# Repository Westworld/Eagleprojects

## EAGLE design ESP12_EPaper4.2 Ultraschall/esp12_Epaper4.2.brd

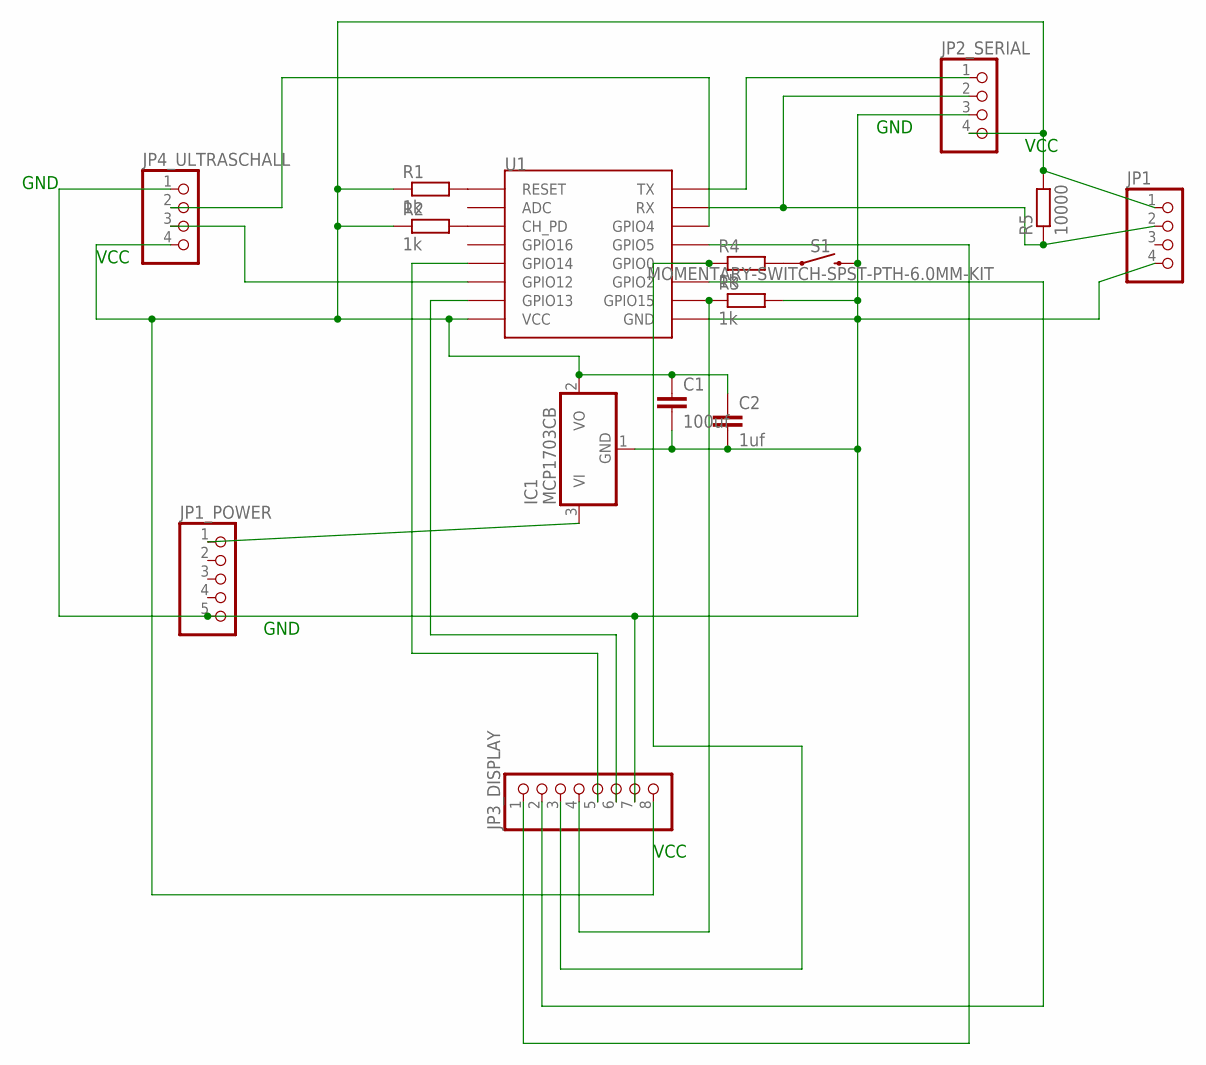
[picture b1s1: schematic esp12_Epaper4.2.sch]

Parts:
C1: 100uf; C025-050X050
C2: 1uf; C025-050X050
IC1: MCP1703CB; SOT23
JP1, JP4_ULTRASCHALL: PINHD-1X4; 1X04
JP1_POWER: PINHD-1X5; 1X05
JP2_SERIAL: PINHD-1X4/90; 1X04/90
JP3_DISPLAY: PINHD-1X8/90; 1X08/90
R1, R2, R3, R4: 1k; R1206
R5: 10000; M1206
S1: MOMENTARY-SWITCH-SPST-PTH-6.0MM-KIT; TACTILE_SWITCH_PTH_6.0MM_KIT
U1: ESP12

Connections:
GND: C1.2, C2.2, IC1.1 (GND), JP1.4, JP1_POWER.5, JP2_SERIAL.3, JP3_DISPLAY.7, JP4_ULTRASCHALL.1, R3.2, S1.3 (2), U1.GND
unnamed: R1.2, U1.RESET
unnamed: R2.2, U1.CH_PD
unnamed: JP3_DISPLAY.3, R4.1, U1.GPIO0
unnamed: JP4_ULTRASCHALL.2, U1.GPIO4
unnamed: R4.2, S1.1
unnamed: JP2_SERIAL.1, U1.TX
unnamed: JP1.2, JP2_SERIAL.2, R5.1, U1.RX
unnamed: IC1.3 (VI), JP1_POWER.1
unnamed: JP3_DISPLAY.5, U1.GPIO14
unnamed: JP3_DISPLAY.6, U1.GPIO13
unnamed: JP3_DISPLAY.2, U1.GPIO2
unnamed: JP3_DISPLAY.1, U1.GPIO5
unnamed: JP4_ULTRASCHALL.3, U1.GPIO12
unnamed: JP3_DISPLAY.4, R3.1, U1.GPIO15
VCC: C1.1, C2.1, IC1.2 (VO), JP1.1, JP2_SERIAL.4, JP3_DISPLAY.8, JP4_ULTRASCHALL.4, R1.1, R2.1, R5.2, U1.VCC

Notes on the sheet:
GND
VCC

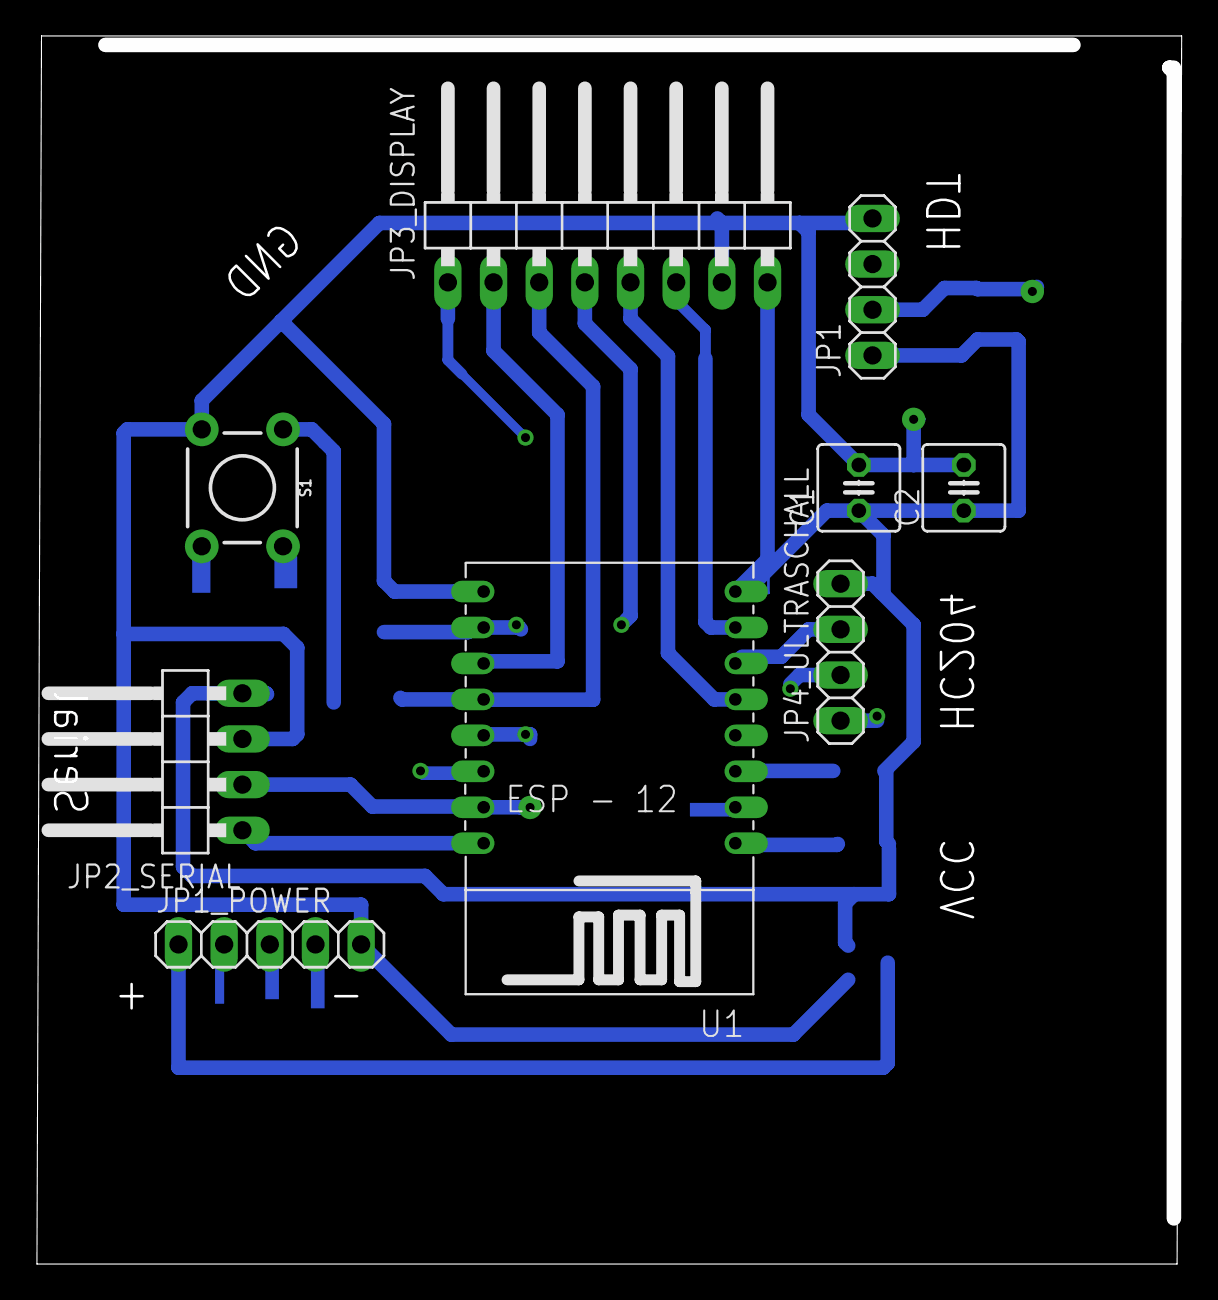
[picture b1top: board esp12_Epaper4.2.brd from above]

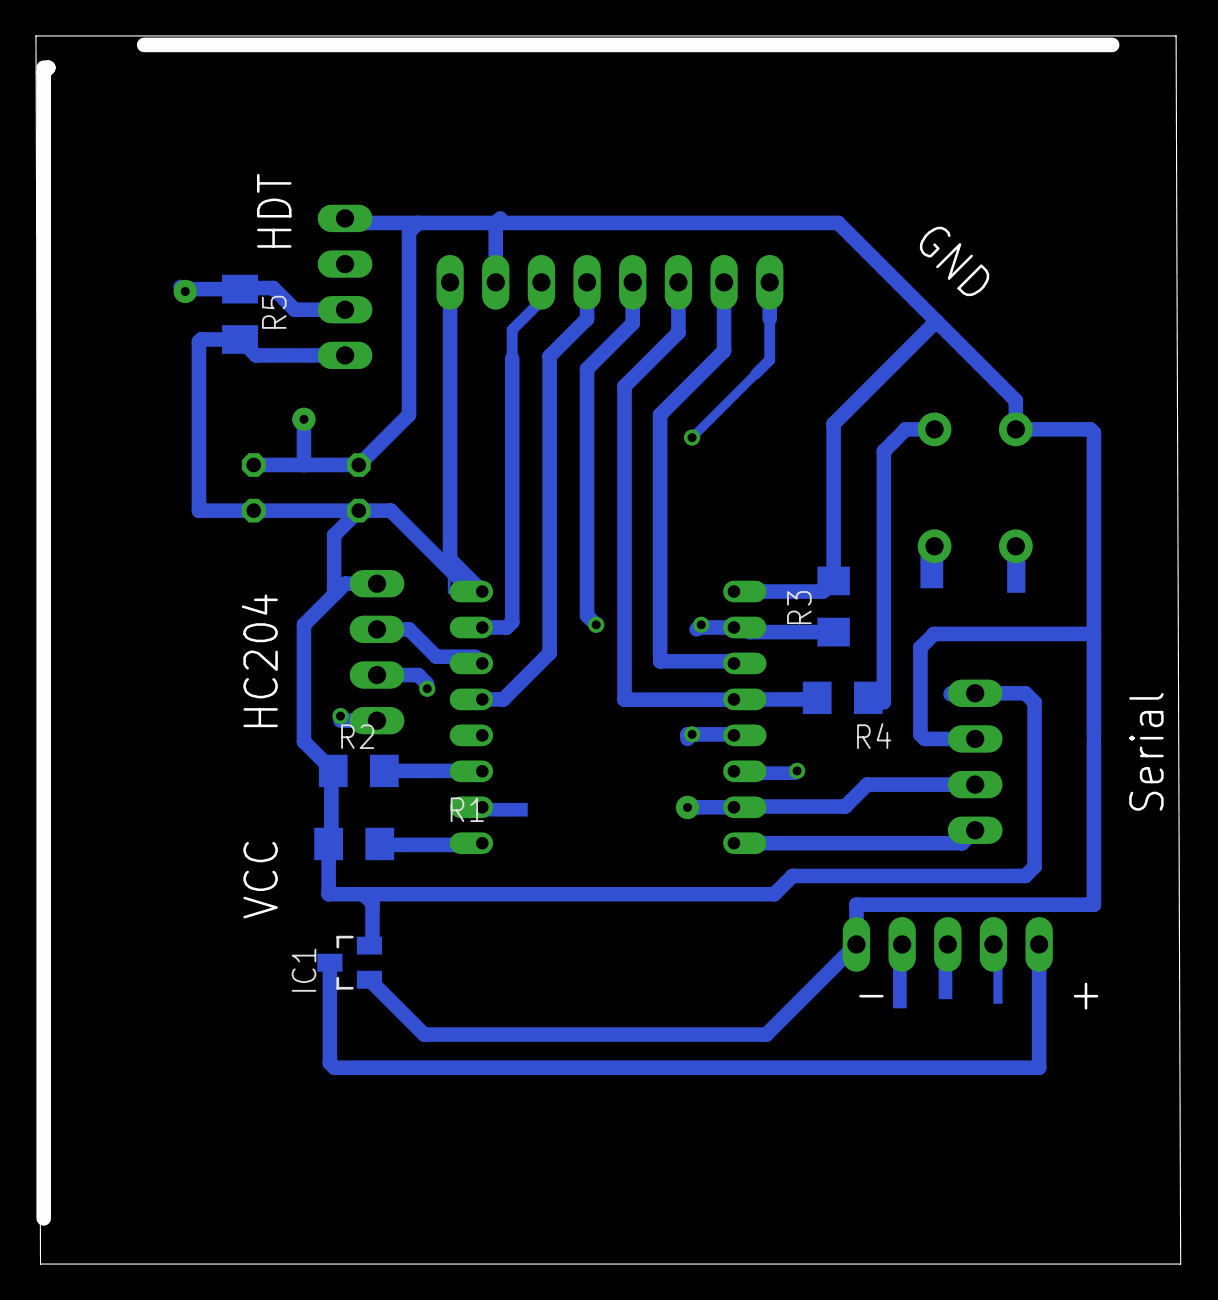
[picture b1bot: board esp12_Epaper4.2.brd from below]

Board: 2 copper layers, 63.7 x 68.3 mm, 15 parts (6 on the bottom side), 16 nets.

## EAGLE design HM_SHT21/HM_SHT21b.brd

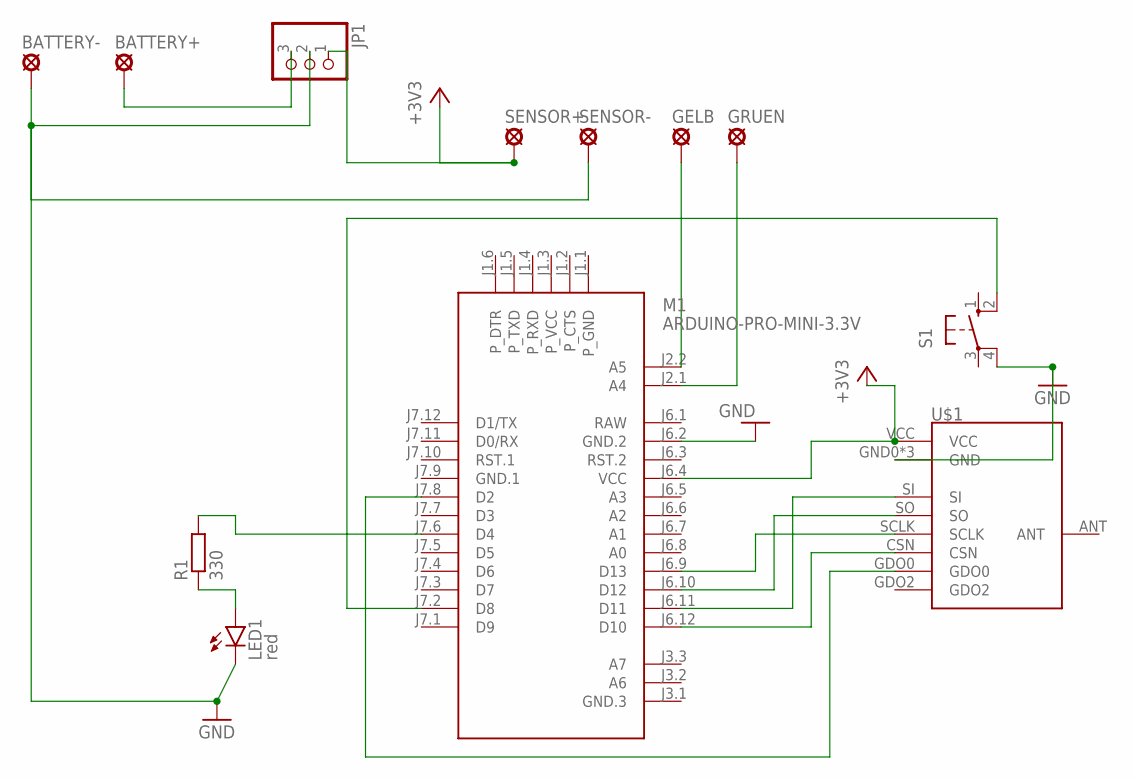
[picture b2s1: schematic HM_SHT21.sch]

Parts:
BATTERY+: LSP11
BATTERY-: LSP11
GELB: LSP11
GRUEN: LSP11
JP1: PINHD-1X3; 1X03
LED1: red; LED5MM
M1: ARDUINO-PRO-MINI-3.3V; ARDUINO-PRO-MINI
R1: 330; 0204/7
S1: 10-XX; B3F-10XX
SENSOR+: LSP11
SENSOR-: LSP11
U$1: CC1101

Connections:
+3V3: JP1.1, M1.J6.4 (VCC), SENSOR+.MP, U$1.VCC
GND: BATTERY-.MP, JP1.2, LED1.K (C), M1.J6.2 (GND.2), S1.4 (P1), SENSOR-.MP, U$1.GND0 (GND), U$1.GND1 (GND), U$1.GND2 (GND)
GND.1: M1.J7.9 (GND.1)
unnamed: M1.J6.12 (D10), U$1.CSN
unnamed: M1.J7.8 (D2), U$1.GDO0
unnamed: M1.J6.11 (D11), U$1.SI
unnamed: M1.J6.10 (D12), U$1.SO
unnamed: M1.J6.9 (D13), U$1.SCLK
unnamed: LED1.A, R1.1
unnamed: M1.J7.2 (D8), S1.2 (S1)
unnamed: M1.J7.6 (D4), R1.2
unnamed: GELB.MP, M1.J2.2 (A5)
unnamed: GRUEN.MP, M1.J2.1 (A4)
RAW: M1.J6.1 (RAW)
VIN: BATTERY+.MP, JP1.3

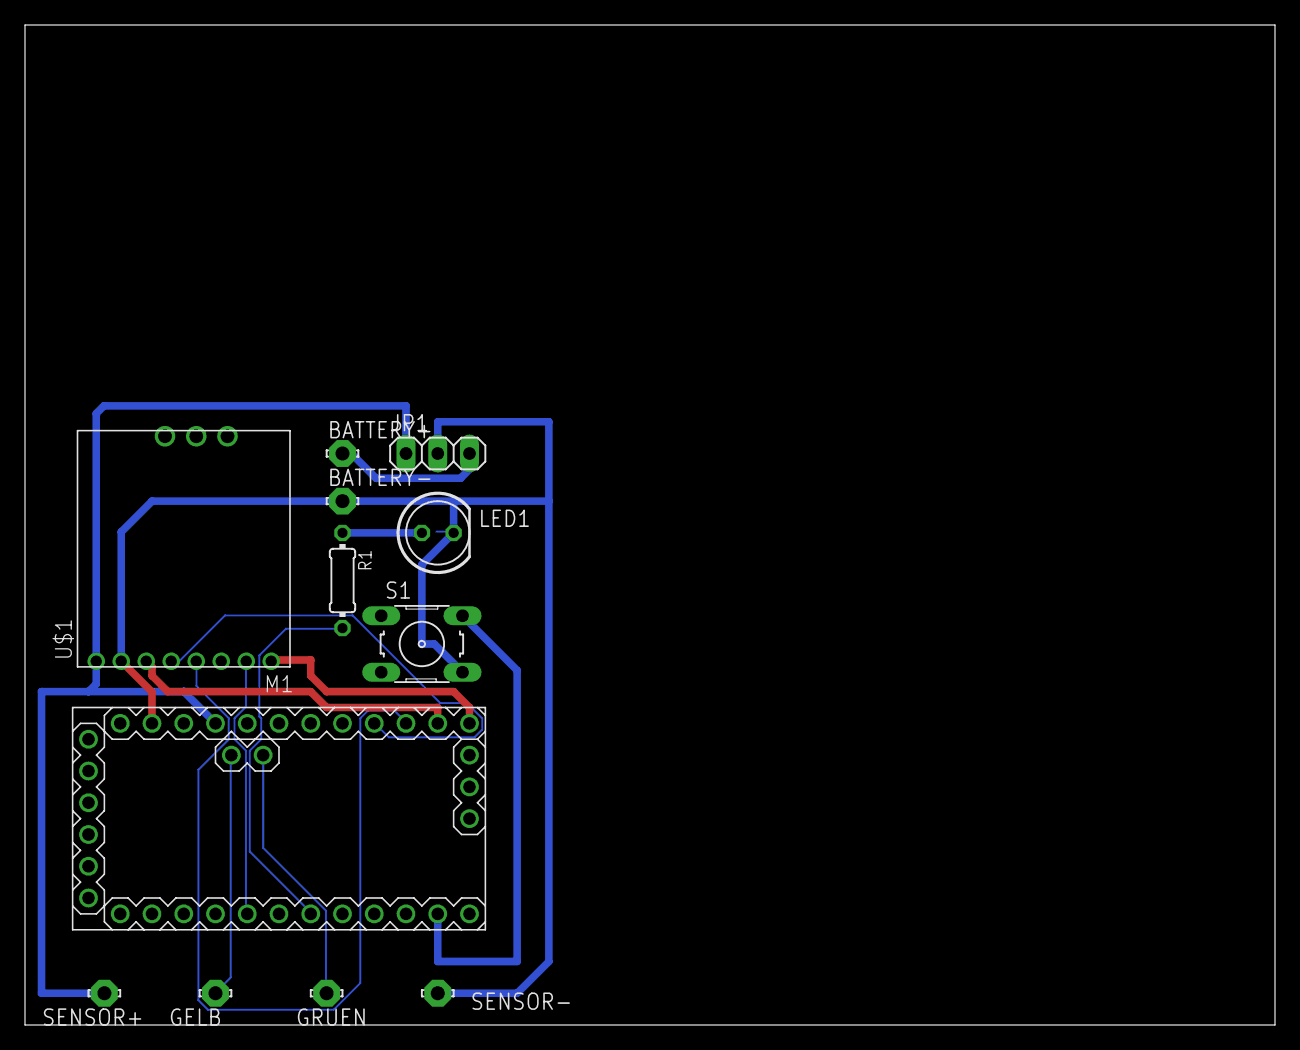
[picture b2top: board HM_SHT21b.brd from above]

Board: 2 copper layers, 100.0 x 80.0 mm, 12 parts (0 on the bottom side), 13 nets.

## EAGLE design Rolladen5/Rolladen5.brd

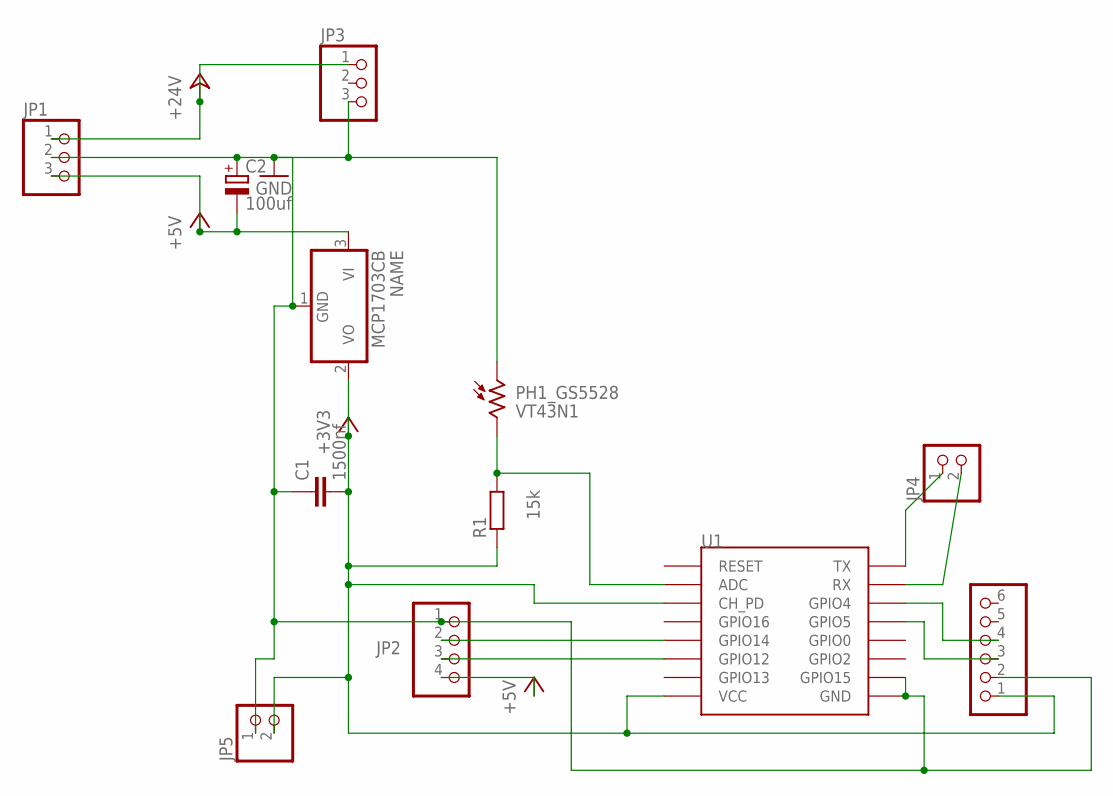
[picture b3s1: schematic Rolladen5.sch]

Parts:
C1: 1500nf; C025-024X044
C2: 100uf; E2,5-6
IC1_MCP1700: MCP1703CB; SOT23
JP1: PINHD-1X3/90; 1X03/90
JP2: PINHD-1X4; 1X04
JP3: PINHD-1X3; 1X03
JP3TMP102: PINHD-1X6; 1X06
JP4, JP5: PINHD-1X2; 1X02
PH1_GS5528: VT43N1; VT400
R1: 15k; 0207/10
U1: ESP12

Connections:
+3V3: C1.2, IC1_MCP1700.2 (VO), JP3TMP102.1, JP5.2, R1.1, U1.CH_PD, U1.VCC
+5V: C2.-, IC1_MCP1700.3 (VI), JP1.3, JP2.4
+24V: JP1.1, JP3.1
GND: C1.1, C2.+, IC1_MCP1700.1 (GND), JP1.2, JP2.1, JP3.3, JP3TMP102.2, JP5.1, PH1_GS5528.1, U1.GND, U1.GPIO15
unnamed: PH1_GS5528.2, R1.2, U1.ADC
unnamed: JP3TMP102.3, U1.GPIO5
unnamed: JP2.3, U1.GPIO12
unnamed: JP4.1, U1.TX
unnamed: JP4.2, U1.RX
unnamed: JP3TMP102.4, U1.GPIO4
unnamed: JP2.2, U1.GPIO14

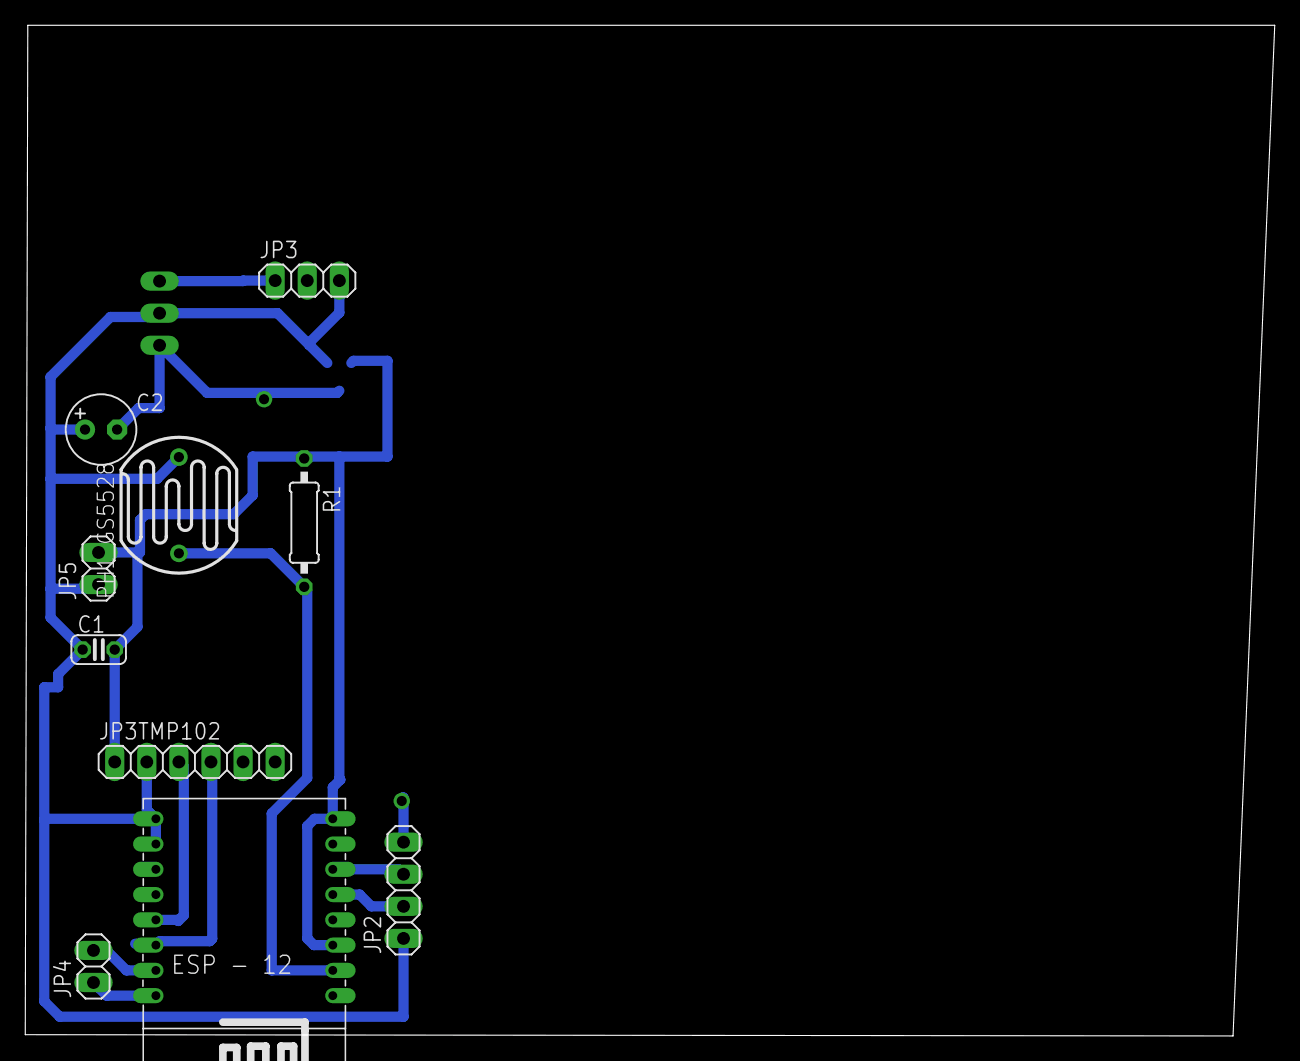
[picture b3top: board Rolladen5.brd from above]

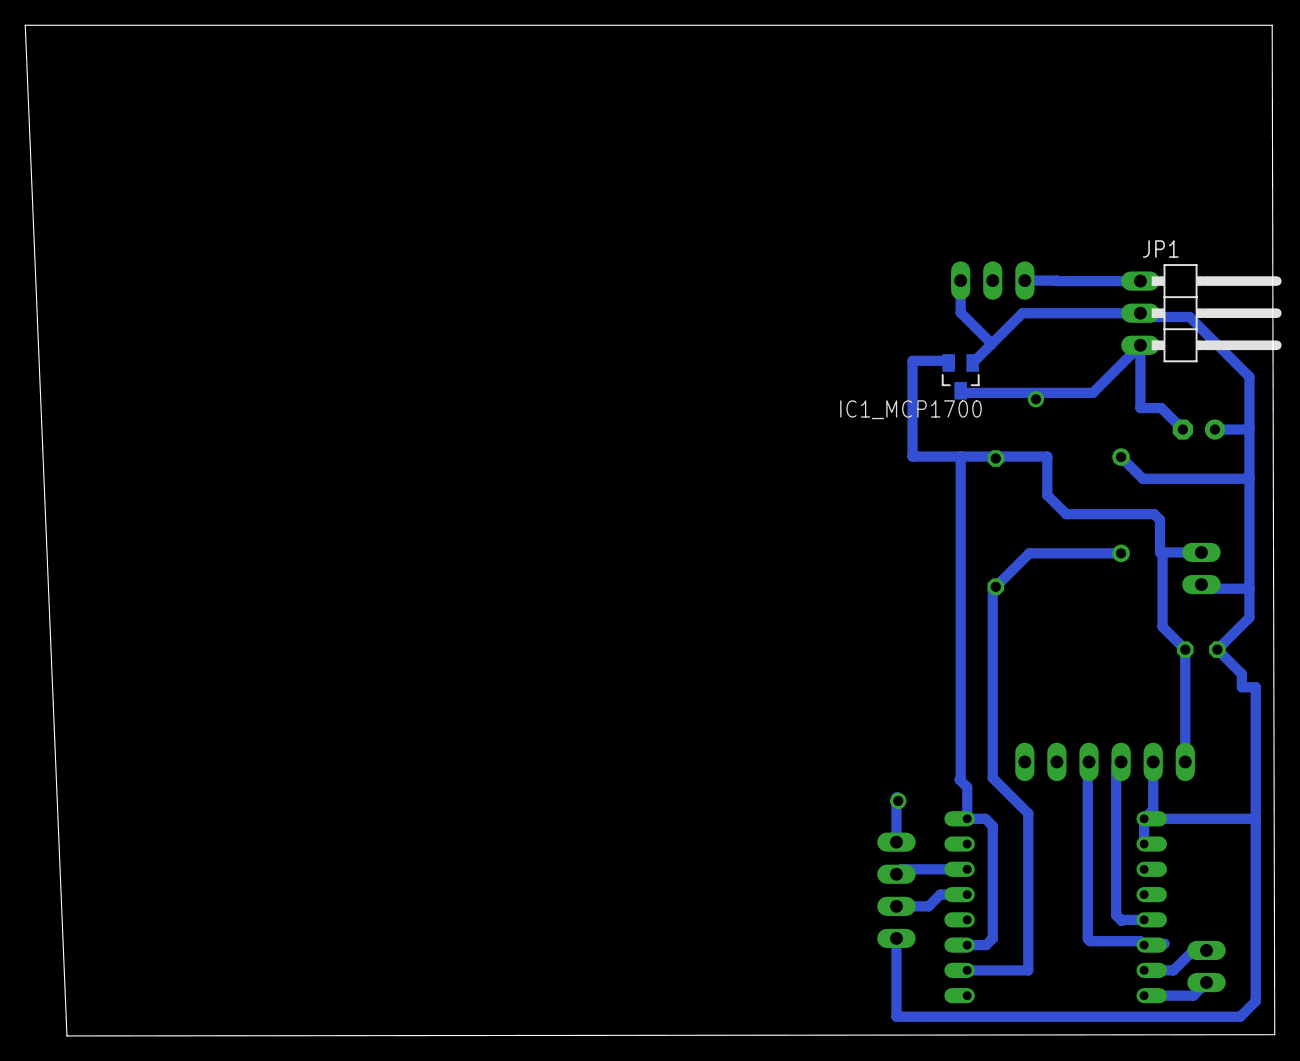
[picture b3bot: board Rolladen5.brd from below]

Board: 2 copper layers, 98.9 x 80.0 mm, 12 parts (2 on the bottom side), 11 nets.

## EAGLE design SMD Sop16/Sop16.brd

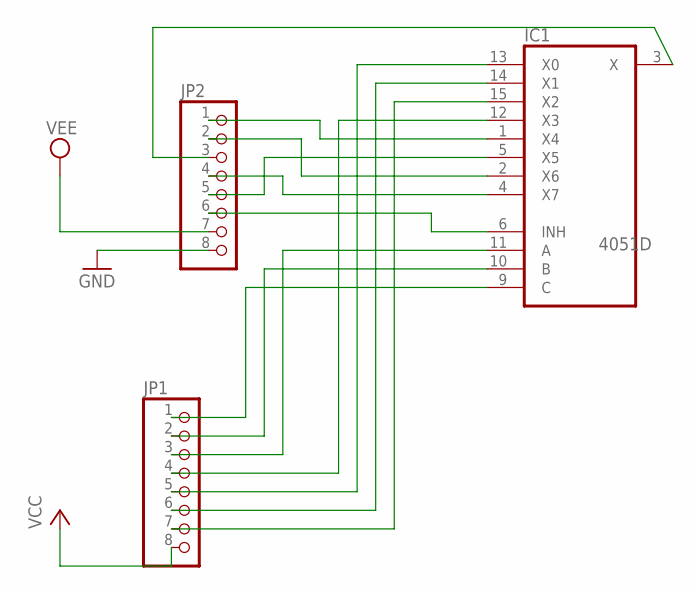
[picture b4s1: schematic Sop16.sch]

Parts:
IC1: 4051D; SO16
JP1, JP2: PINHD-1X8; 1X08

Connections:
GND: IC1.8 (GND), JP2.8
unnamed: IC1.1 (X4), JP2.1
unnamed: IC1.2 (X6), JP2.2
unnamed: IC1.3 (X), JP2.3
unnamed: IC1.4 (X7), JP2.4
unnamed: IC1.5 (X5), JP2.5
unnamed: IC1.6 (INH), JP2.6
unnamed: IC1.9 (C), JP1.1
unnamed: IC1.10 (B), JP1.2
unnamed: IC1.11 (A), JP1.3
unnamed: IC1.12 (X3), JP1.4
unnamed: IC1.13 (X0), JP1.5
unnamed: IC1.14 (X1), JP1.6
unnamed: IC1.15 (X2), JP1.7
VCC: IC1.16 (VCC), JP1.8
VEE: IC1.7 (VEE), JP2.7

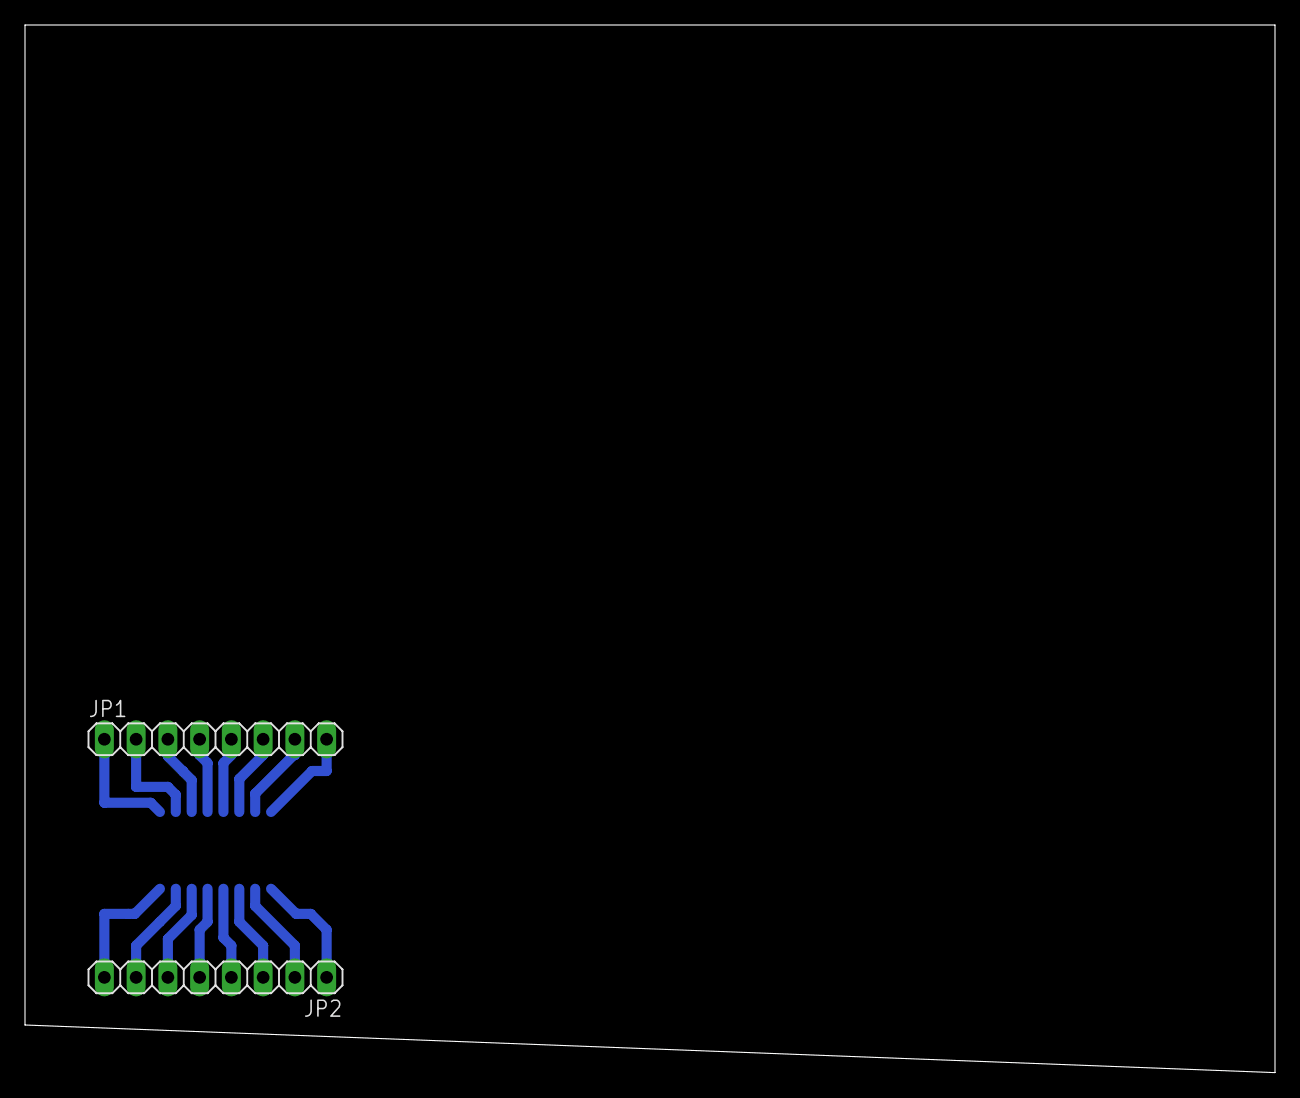
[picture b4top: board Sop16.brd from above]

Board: 2 copper layers, 100.0 x 83.8 mm, 3 parts (1 on the bottom side), 16 nets.

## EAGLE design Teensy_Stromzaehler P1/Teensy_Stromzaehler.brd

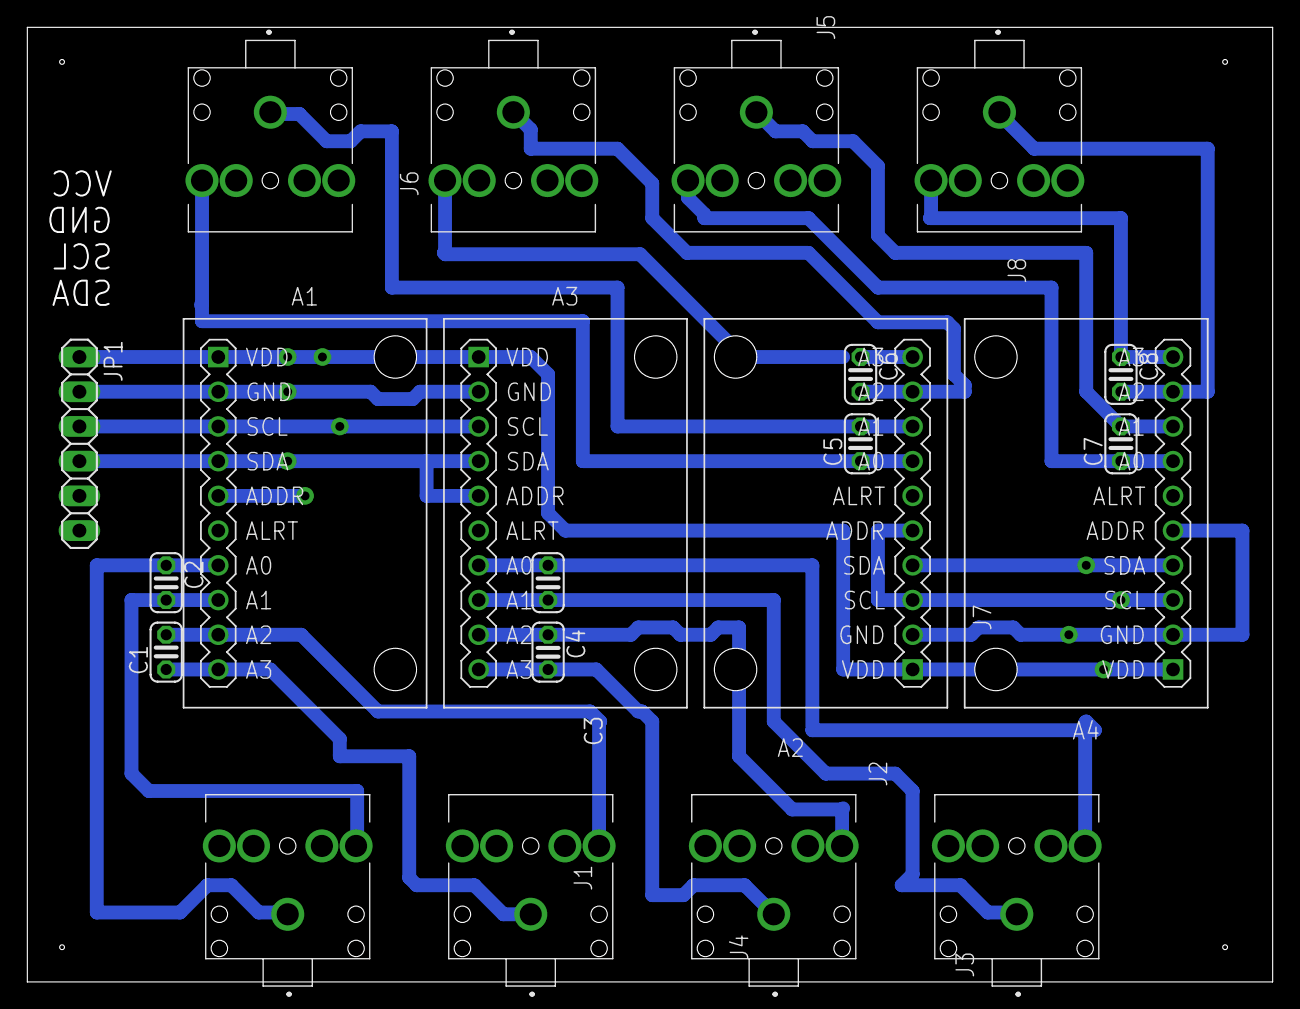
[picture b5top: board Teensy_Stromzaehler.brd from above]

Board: 2 copper layers, 91.1 x 69.8 mm, 21 parts (0 on the bottom side), 20 nets.

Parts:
A1, A2, A3, A4: ADC-4CH-ADS1115
C1, C2, C4, C5, C6, C7, C8: 100nf; C025-024X044
C3: 110nf; C025-024X044
J1, J2, J3, J4, J5, J6, J7, J8: FC68133
JP1: 1X06

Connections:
unnamed: A1.7, C2.1, J2.1
unnamed: A1.8, C2.2, J2.2
unnamed: A1.9, C1.2, J1.2
unnamed: A1.10, C1.1, J1.1
unnamed: A3.8, C3.2, J3.1
unnamed: A3.10, C4.2, J4.1
unnamed: A4.7, C7.1, J5.2
unnamed: A3.7, C3.1, J3.2
unnamed: A1.2, A2.2, A3.2, A4.2, A4.5, JP1.2
unnamed: A2.7, C5.1, J6.2
unnamed: A2.8, C5.2, J6.1
unnamed: A1.3, A2.3, A2.5, A3.3, A4.3, JP1.3
unnamed: A2.10, C6.1, J7.2
unnamed: A2.9, C6.2, J7.1
unnamed: A1.4, A2.4, A3.4, A3.5, A4.4, JP1.4
unnamed: A3.9, C4.1, J4.2
unnamed: A4.8, C7.2, J5.1
unnamed: A4.9, C8.2, J8.1
unnamed: A4.10, C8.1, J8.2
VDD: A1.1, A1.5, A2.1, A3.1, A4.1, JP1.1

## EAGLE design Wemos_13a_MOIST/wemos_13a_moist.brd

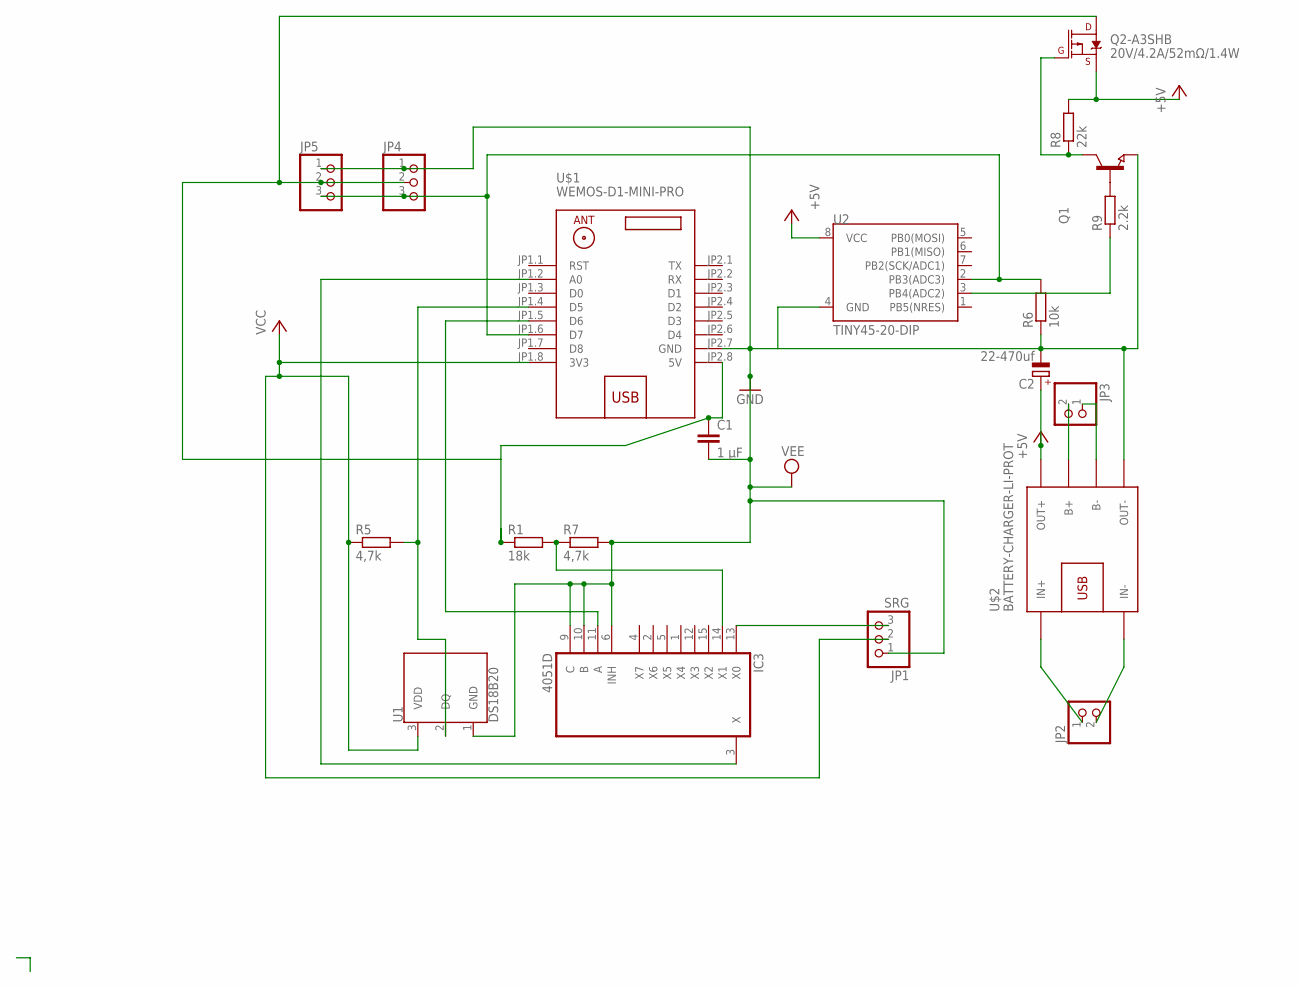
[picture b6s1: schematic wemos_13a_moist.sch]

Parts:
C1: 1 μF; C025-024X044
C2: 22-470uf; E2,5-5
IC3: 4051D; SO16
JP1: SRG; 1X03/90
JP2, JP3: PINHD-1X2; 1X02
JP4, JP5: PINHD-1X3; 1X03
Q1: NPN-TRANSISTOR_SOT23; SOT23
Q2-A3SHB: 20V/4.2A/52mΩ/1.4W; SOT23-3
R1: 18k; 0204/7
R5, R7: 4,7k; M1206
R6: 10k; M1206
R8: 22k; M1206
R9: 2.2k; M1206
U1: DS18B20; TO-92-AMMO
U2: TINY45-20-DIP; DIP08_MCU
U$1: WEMOS-D1-MINI-PRO
U$2: BATTERY-CHARGER-LI-PROT

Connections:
+5V: C2.+, Q1.3 (C), Q2-A3SHB.1 (G), Q2-A3SHB.2 (S), R8.1, R8.2, U2.8 (VCC), U$2.OUT+
GND: C1.2, C2.-, IC3.6 (INH), IC3.7 (VEE), IC3.8 (GND), IC3.9 (C), IC3.10 (B), JP1.1, JP4.1, JP5.1, Q1.2 (E), R6.1, R7.2, U1.1 (GND), U2.4 (GND), U$1.JP2.7 (GND), U$2.OUT-
unnamed: JP3.2, U$2.B+
unnamed: IC3.14 (X1), R1.2, R7.1
unnamed: IC3.11 (A), U$1.JP1.5 (D6)
unnamed: IC3.3 (X), U$1.JP1.2 (A0)
unnamed: JP3.1, U$2.B-
unnamed: JP2.1, U$2.IN+
unnamed: IC3.13 (X0), JP1.3
unnamed: R9.1, U2.3 (PB4(ADC2))
unnamed: JP4.3, JP5.3, R6.2, U2.2 (PB3(ADC3)), U$1.JP1.6 (D7)
unnamed: Q1.1 (B), R9.2
unnamed: JP2.2, U$2.IN-
unnamed: C1.1, JP4.2, JP5.2, Q2-A3SHB.3 (D), R1.1, U$1.JP2.8 (5V)
TEMP: R5.2, U1.2 (DQ), U$1.JP1.4 (D5)
VCC: IC3.16 (VCC), JP1.2, R5.1, U1.3 (VDD), U$1.JP1.8 (3V3)

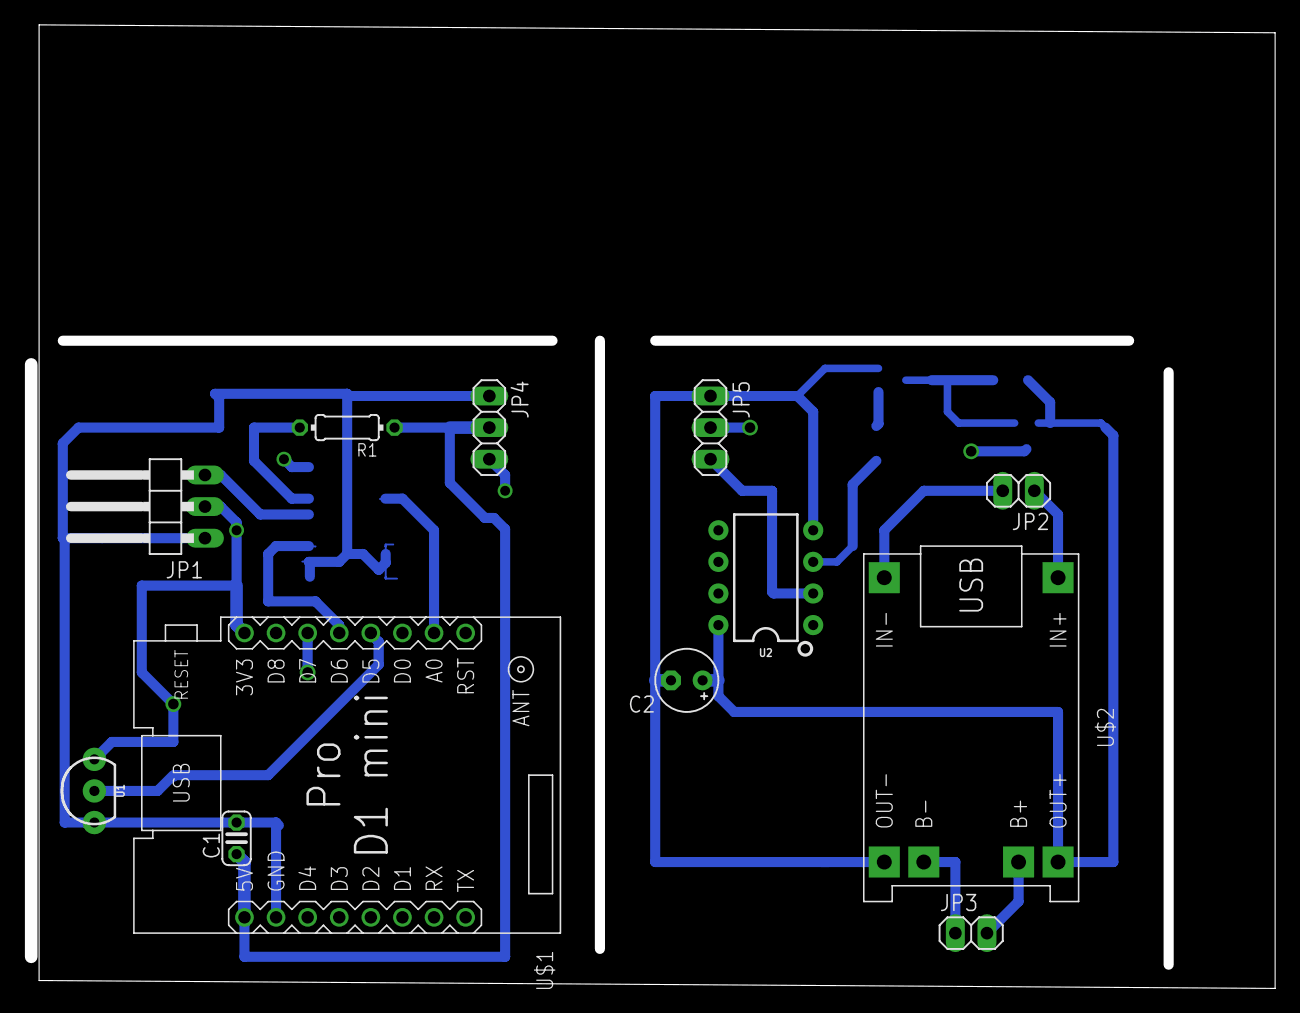
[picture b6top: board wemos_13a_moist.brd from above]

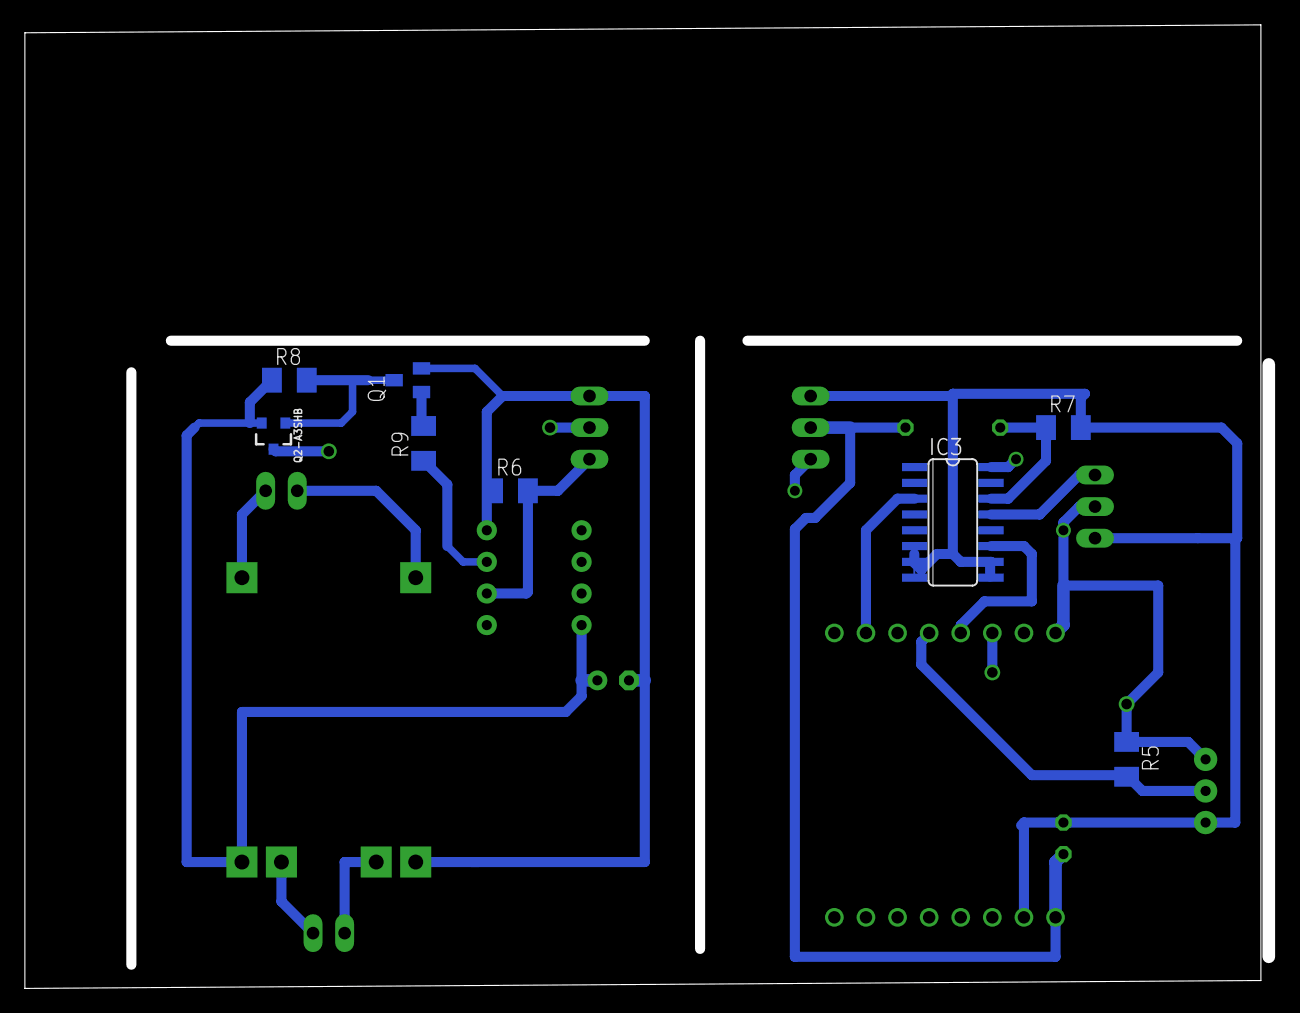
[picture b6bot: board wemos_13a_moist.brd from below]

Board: 2 copper layers, 100.0 x 77.5 mm, 20 parts (8 on the bottom side), 16 nets.

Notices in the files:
parts and their libraries:
SparkFun-Switches: Licensing: Creative Commons ShareAlike 4.0 International - https://creativecommons.org/licenses/by-sa/4.0
diy-modules: Released under the Creative Commons Attribution 4.0 International License: http://creativecommons.org/licenses/by/4.0
